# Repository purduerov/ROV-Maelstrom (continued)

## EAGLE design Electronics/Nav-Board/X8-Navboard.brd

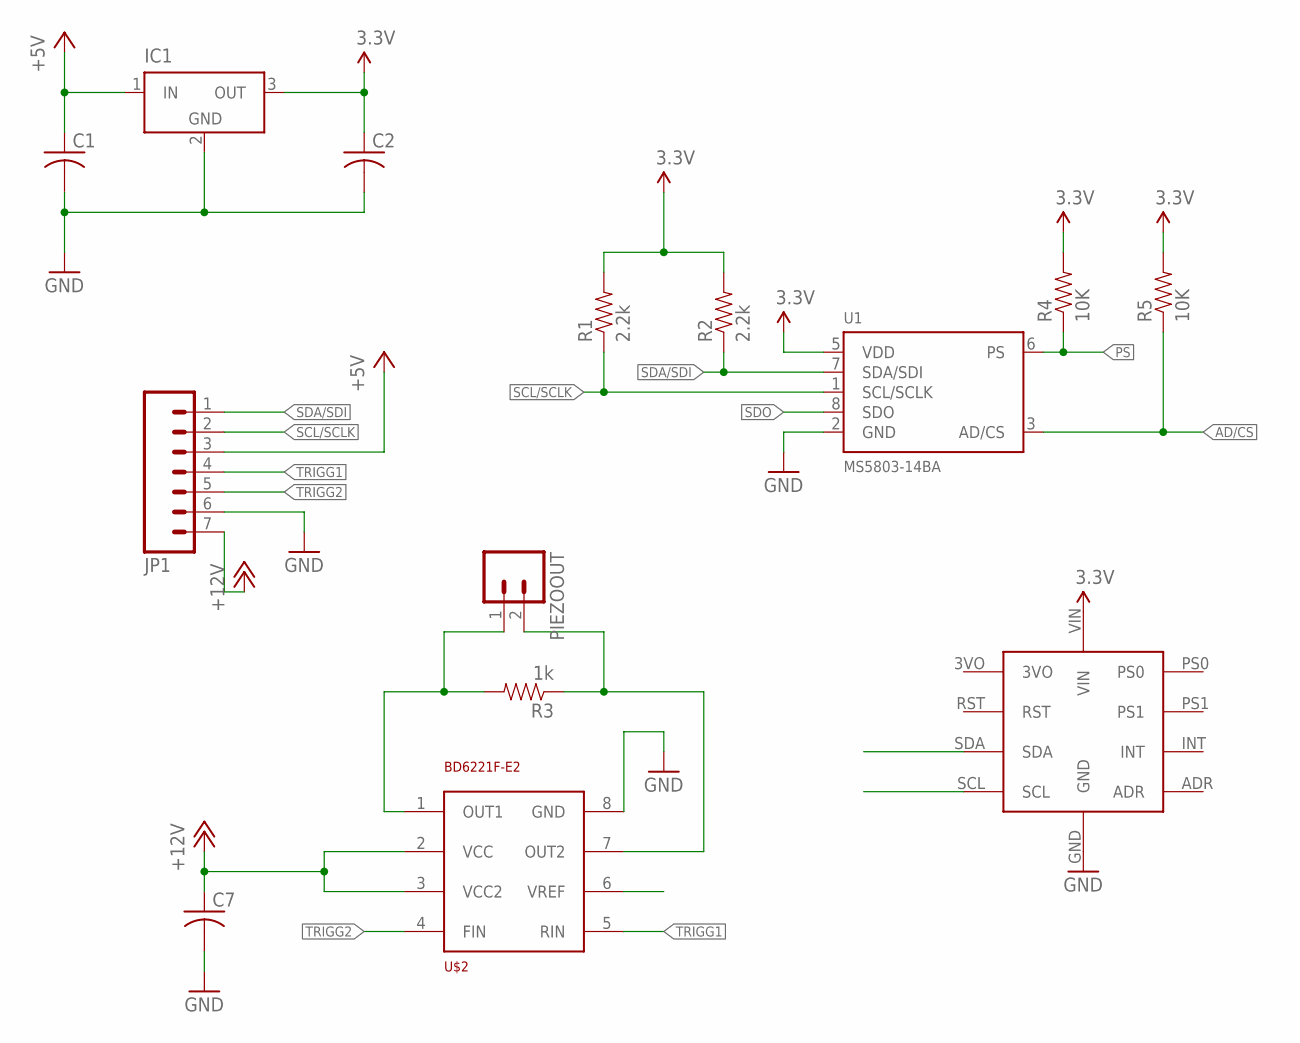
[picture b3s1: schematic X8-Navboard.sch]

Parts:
C1, C2, C7: C-USC0603; C0603
IC1: LT1129CST5; SOT223
JP1: M07; 1X07
PIEZOOUT: M02LOCK_LONGPADS; 1X02_LOCK_LONGPADS
R1, R2: 2.2k; 0603-RES
R3: 1k; 0603-RES
R4, R5: 10K; 0603-RES
U1: MS5803-14BA; MS5803
U$1: BNO055_9DOF_BREAKOUT; BNO055
U$2: BD6221F-E2; SOIC8

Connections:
3.3V: C2.1, IC1.3 (OUT), R1.2, R2.2, R4.2, R5.2, U1.5 (VDD), U$1.VIN
+5V: C1.1, IC1.1 (IN), JP1.3
+12V: C7.1, JP1.7, U$2.2 (VCC), U$2.3 (VCC2)
AD/CS: R5.1, U1.3 (AD/CS)
GND: C1.2, C2.2, C7.2, IC1.2 (GND), IC1.4 (GND), JP1.6, U1.2 (GND), U$1.GND, U$2.8 (GND)
unnamed: PIEZOOUT.1, R3.2, U$2.1 (OUT1)
unnamed: PIEZOOUT.2, R3.1, U$2.7 (OUT2)
PS: R4.1, U1.6 (PS)
SCL/SCLK: JP1.2, R1.1, U1.1 (SCL/SCLK), U$1.SCL
SDA/SDI: JP1.1, R2.1, U1.7 (SDA/SDI), U$1.SDA
SDO: U1.8 (SDO)
TRIGG1: JP1.4, U$2.5 (RIN)
TRIGG2: JP1.5, U$2.4 (FIN)

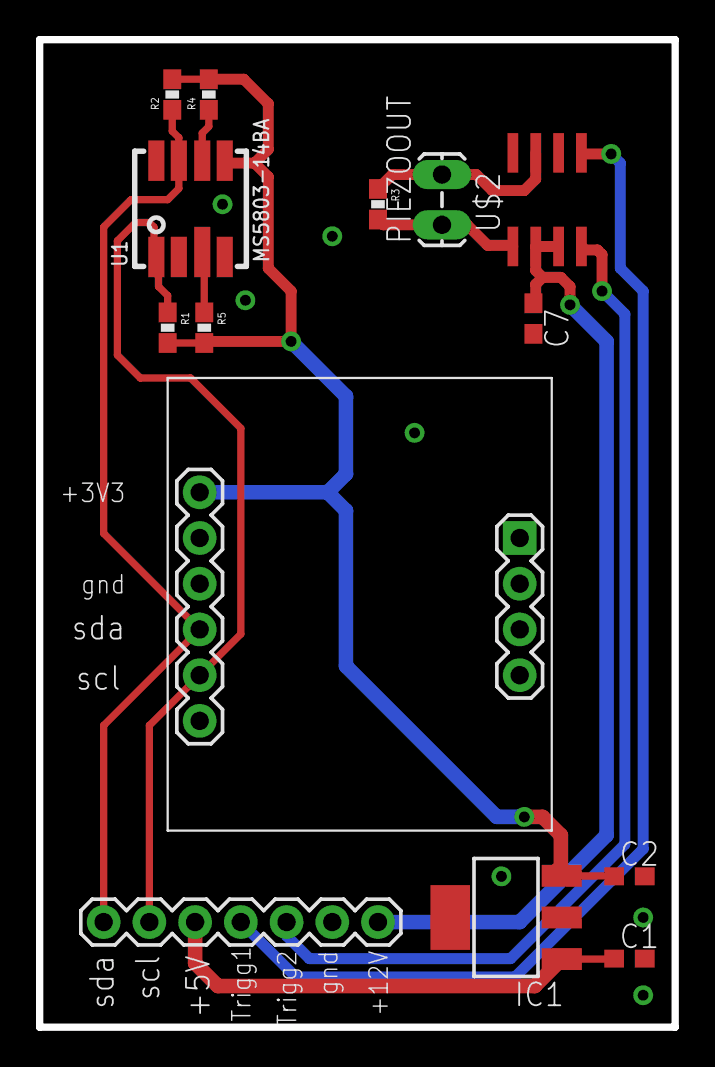
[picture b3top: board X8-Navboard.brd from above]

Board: 2 copper layers, 35.3 x 54.9 mm, 14 parts (0 on the bottom side), 12 nets.

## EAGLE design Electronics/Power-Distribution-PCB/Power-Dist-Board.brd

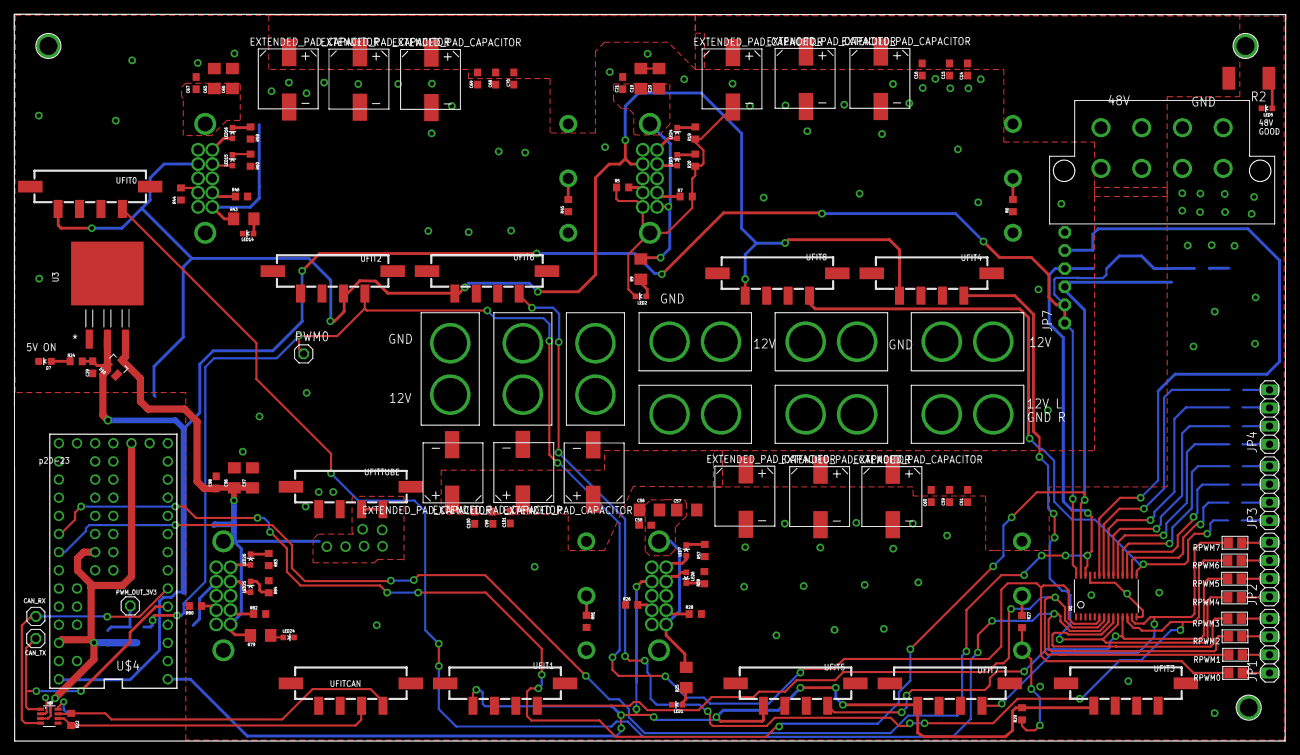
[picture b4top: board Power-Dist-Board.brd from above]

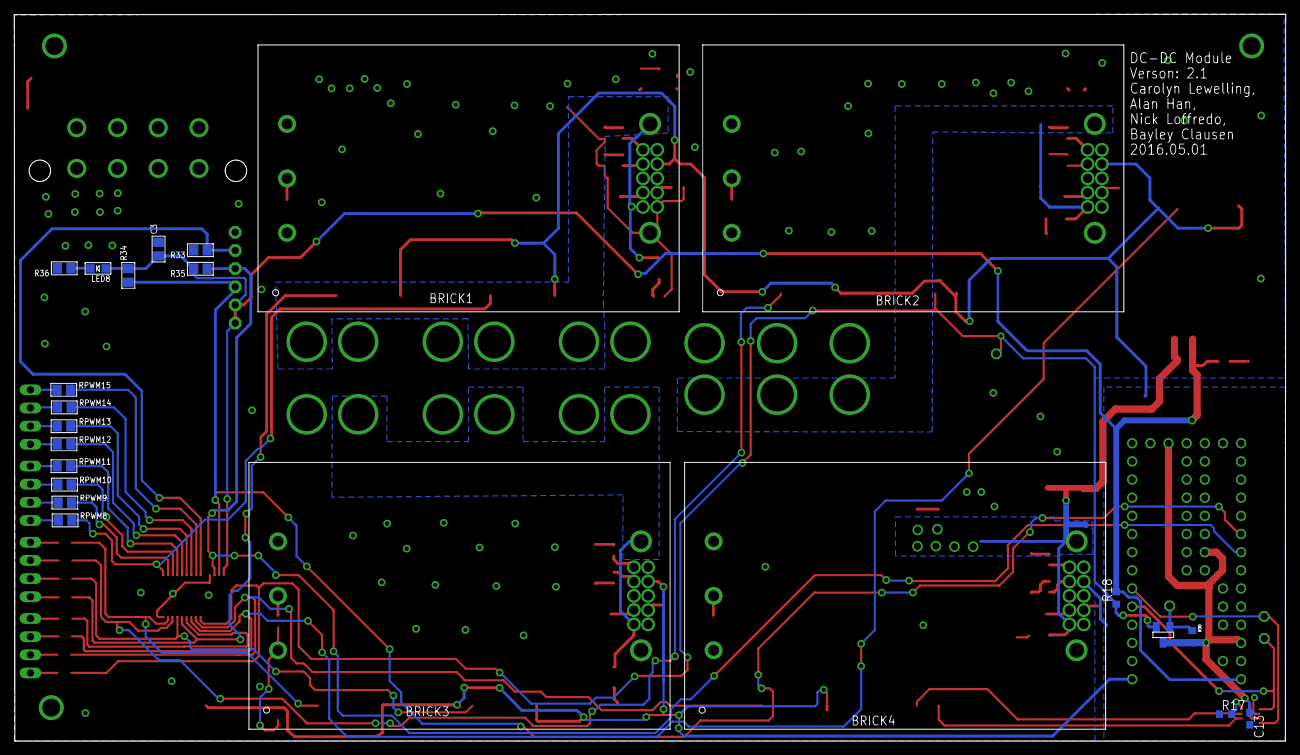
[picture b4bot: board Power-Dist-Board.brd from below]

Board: 2 copper layers, 177.9 x 101.7 mm, 148 parts (23 on the bottom side), 85 nets.

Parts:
BRICK1, BRICK2, BRICK3, BRICK4: BRICK_DC-DC_CONVERTER
C3: 10uF; 0805
C13: 0.1uF; C0603
C14, C15, C16: .1uF; C0603
C19, C20: 15uF; C3216
C21: 10uF; C0603
C22V1, C22V2, C22V3, C22V4, C22V5, C22V6, C22V7, C22V8, C22V9, C22V10, C22V11, C22V12: EXTENDED_PAD_CAPACITOR; MODIFIED-NICHICON-UX-8X10
C29: 0.1u; C0603
C56, C57, C65, C66, C96, C97: 15u; C3216
C58, C67, C98: 10u; C0603
C59, C60, C61, C68, C69, C70, C99, C100, C101: .1u; C0603
CAN_RX: 1X01
CAN_TX: 1X01
D7: RED; LED-0603
D10: BAS40; SOT23
JP1, JP2, JP3, JP4: 1X04
JP7: 1X06-CLEANBIG
LED1, LED2, LED3, LED5, LED6, LED14, LED15, LED24, LED25: GREEN; LED-0603
LED4, LED7, LED16, LED26: RED; LED-0603
LED8: VCC; CHIPLED_0805
PWM0: 1X01
PWM_OUT_3V3: 1X01
R2: 2700; R2512
R5, R7, R28, R46, R82: 10k; R0603
R6, R27, R29, R45, R81: 0; R0603
R9, R25, R43, R79: 1.1k; R1206
R17, R22: 120; R0603
R18, R30: 10K; R0603
R19, R20, R57, R58, R59, R60, R83, R84: 1k; R0603
R24: 330; R0603
R26: 33k; R0603
R33, R34, R35: 10K; 0805
R36: 220; 0805
R44: 22k; R0603
R80: 47k; R0603
RPWM0, RPWM1, RPWM2, RPWM3, RPWM4, RPWM5, RPWM6, RPWM7, RPWM8, RPWM9, RPWM10, RPWM11, RPWM12, RPWM13, RPWM14, RPWM15: 220; 0805
U1: PCA9685; TSSOP28
U3: LM1085IS-5.0; TO254P1435X457-3N
U$2, U$3, U$10, U$11, U$16, U$17, U$18, U$19, U$21: XT60
U$4: TEENSY_3.1_ALL_PINS_AND_PADS; TEENSY3_ALL_PINS_&_PADS
U$8: MAX3051MAX3051; SOT23-8L
U$12: BSS138; SOT-23-BSS138
U$13: MEGA-FIT-8
U$100, U$101, U$102: MOUNTINGHOLE2.5; MOUNTINGHOLE_2.5_PLATED
UFIT0, UFIT1, UFIT2, UFIT3, UFIT4, UFIT5, UFIT6, UFIT7, UFIT8: MICRO-FIT-4-SMD-HZVT; MICRO-FIT-4-SMD(CORRECTED)
UFITCAN: MICRO-FIT-4-SMD-HZVT; MICRO-FIT-4-SMD(CORRECTED)
UFITTUBE: MICRO-FIT-4-SMD-HZVT; MICRO-FIT-4-SMD(CORRECTED)

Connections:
+3V3: C13.1, R30.2, U$4.3.3V, U$4.3.3V1, U$4.3.3V2, U$8.3, U$12.1
+5V: C3.1, C29.2, D10.1, JP7.1, JP7.2, LED8.A, R18.2, R24.2, R34.2, R35.2, U1.28, U3.2, U$4.VIN
+12V1: BRICK1.6, BRICK1.16, C19.1, C20.1, C21.1, R9.2, U$2.P$2, U$3.P$2, U$10.P$2
+12V2: BRICK2.6, BRICK2.16, C65.1, C66.1, C67.1, R43.2, U$11.P$2, U$16.P$2, U$17.P$2
+12V3: BRICK3.6, BRICK3.16, C56.1, C57.1, C58.1, R25.2, U$18.P$2, U$19.P$2, U$21.P$2
+12V4: BRICK4.6, BRICK4.16, C96.1, C97.1, C98.1, D10.3, R79.2, U3.3, UFITTUBE.C3, UFITTUBE.C4
+48V: BRICK1.1, BRICK2.1, BRICK3.1, BRICK4.1, C14.1, C15.1, C16.1, C22V1.P$3, C22V2.P$3, C22V3.P$3, C22V4.P$3, C22V5.P$3, C22V6.P$3, C22V7.P$3, C22V8.P$3, C22V9.P$3, C22V10.P$3, C22V11.P$3, C22V12.P$3, C59.1, C60.1, C61.1, C68.1, C69.1, C70.1, C99.1, C100.1, C101.1, R2.2, U$13.P1, U$13.P2, U$13.P5, U$13.P6
ADRS00A: BRICK1.8, R7.2
ADRS00A1: BRICK3.8, R28.2
ADRS00A4: BRICK2.8, R46.2
ADRS00A5: BRICK4.8, R82.2
ADRS00B: BRICK1.9, R5.2
ADRS00B1: BRICK3.9, R26.2
ADRS00B4: BRICK2.9, R44.2
ADRS00B5: BRICK4.9, R80.2
ALERT: BRICK1.14, LED4.A
ALERT2: BRICK2.14, LED16.A
ALERT3: BRICK3.14, LED7.A
ALERT4: BRICK4.14, LED26.A
CANH: R22.2, U$8.7, UFITCAN.C4
CANL: R22.1, U$8.6, UFITCAN.C3
DGND: BRICK1.13, BRICK2.13, BRICK3.13, BRICK4.13, C13.2, R17.1, R29.2, U$4.GND, U$4.GND1, U$4.GND2, U$8.2, UFIT0.C1, UFIT1.C1, UFIT2.C3, UFIT3.C1, UFIT4.C1, UFIT5.C1, UFIT6.C1, UFIT7.C1, UFIT8.C1
GND: BRICK1.4, BRICK1.5, BRICK1.7, BRICK2.4, BRICK2.5, BRICK2.7, BRICK3.4, BRICK3.5, BRICK3.7, BRICK4.4, BRICK4.5, BRICK4.7, C3.2, C14.2, C15.2, C16.2, C19.2, C20.2, C21.2, C22V1.P$1, C22V2.P$1, C22V3.P$1, C22V4.P$1, C22V5.P$1, C22V6.P$1, C22V7.P$1, C22V8.P$1, C22V9.P$1, C22V10.P$1, C22V11.P$1, C22V12.P$1, C29.1, C56.2, C57.2, C58.2, C59.2, C60.2, C61.2, C65.2, C66.2, C67.2, C68.2, C69.2, C70.2, C96.2, C97.2, C98.2, C99.2, C100.2, C101.2, D7.C, JP7.6, LED1.C, LED2.C, LED5.C, LED14.C, LED24.C, R5.1, R6.1, R7.1, R19.1, R20.1, R26.1, R27.1, R28.1, R29.1, R33.2, R36.2, R44.1, R45.1, R46.1, R57.1, R58.1, R59.1, R60.1, R80.1, R81.1, R82.1, R83.1, R84.1, U1.1, U1.2, U1.3, U1.4, U1.5, U1.14, U1.24, U1.25, U3.1, U$2.P$1, U$3.P$1, U$10.P$1, U$11.P$1, U$13.P3, U$13.P4, U$13.P7, U$13.P8, U$16.P$1, U$17.P$1, U$18.P$1, U$19.P$1, U$21.P$1, UFITTUBE.C1, UFITTUBE.C2
unnamed: BRICK1.2, R6.2
unnamed: LED5.A, R2.1
unnamed: LED4.C, R19.2
unnamed: LED3.C, R20.2
unnamed: LED1.A, R25.1
unnamed: LED2.A, R9.1
unnamed: BRICK3.2, R27.2
unnamed: LED8.C, R36.1
unnamed: JP2.3, RPWM6.1
unnamed: JP2.4, RPWM7.1
unnamed: JP2.2, RPWM5.1
unnamed: D7.A, R24.1
unnamed: LED14.A, R43.1
unnamed: JP2.1, RPWM4.1
unnamed: BRICK2.2, R45.2
unnamed: JP1.4, RPWM3.1
unnamed: JP1.3, RPWM2.1
unnamed: JP1.2, RPWM1.1
unnamed: JP1.1, RPWM0.1
unnamed: JP3.1, RPWM8.1
unnamed: JP3.2, RPWM9.1
unnamed: JP3.3, RPWM10.1
unnamed: LED7.C, R57.2
unnamed: LED6.C, R58.2
unnamed: LED16.C, R59.2
unnamed: LED15.C, R60.2
unnamed: JP3.4, RPWM11.1
unnamed: JP4.1, RPWM12.1
unnamed: JP4.2, RPWM13.1
unnamed: JP4.3, RPWM14.1
unnamed: JP4.4, RPWM15.1
unnamed: LED24.A, R79.1
unnamed: BRICK4.2, R81.2
unnamed: LED26.C, R83.2
unnamed: LED25.C, R84.2
unnamed: R17.2, U$8.8
OE: JP7.5, R33.1, U1.23
PG: BRICK1.12, LED3.A
PG2: BRICK2.12, LED15.A
PG3: BRICK3.12, LED6.A
PG4: BRICK4.12, LED25.A
PWM0: PWM0.1, R18.1, RPWM0.2, U1.6, U$12.2, UFIT2.C4
PWM1: RPWM1.2, U1.7, UFIT1.C4
PWM2: RPWM2.2, U1.8, UFIT0.C4
PWM3: RPWM3.2, U1.9
PWM4: RPWM4.2, U1.10, UFIT4.C4
PWM5: RPWM5.2, U1.11, UFIT5.C4
PWM6: RPWM6.2, U1.12, UFIT6.C4
PWM7: RPWM7.2, U1.13, UFIT7.C4
PWM8: RPWM8.2, U1.15, UFIT8.C4
PWM9: RPWM9.2, U1.16
PWM10: RPWM10.2, U1.17
PWM11: RPWM11.2, U1.18
PWM12: RPWM12.2, U1.19
PWM13: RPWM13.2, U1.20
PWM14: RPWM14.2, U1.21
PWM15: RPWM15.2, U1.22
PWM_IN: PWM_OUT_3V3.1, R30.1, U$12.3
RXD: CAN_RX.1, U$4.4, U$8.4
SCL: JP7.4, R35.1, U1.26, U$4.19/A5
SDA: JP7.3, R34.1, U1.27, U$4.18/A4
TXD: CAN_TX.1, U$4.3, U$8.1

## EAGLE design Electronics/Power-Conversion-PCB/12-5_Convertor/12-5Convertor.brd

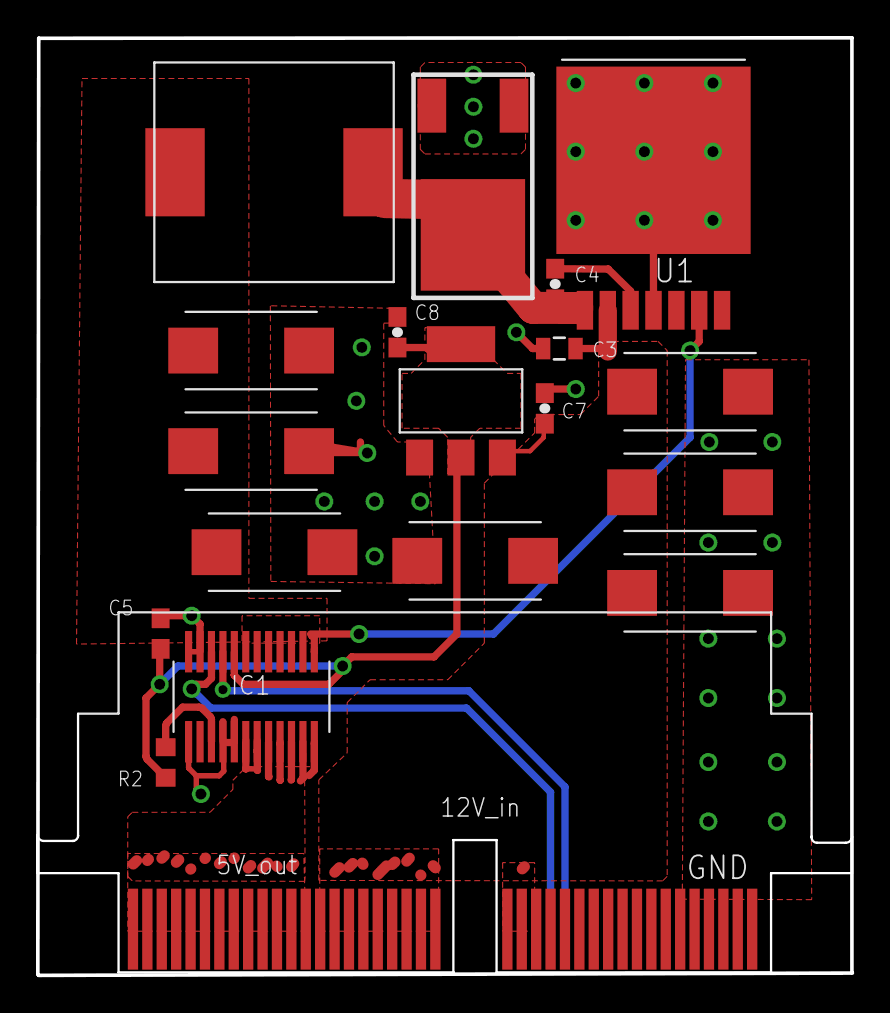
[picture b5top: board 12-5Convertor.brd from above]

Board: 2 copper layers, 45.3 x 52.1 mm, 19 parts (0 on the bottom side), 10 nets.

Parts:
C2, C11, C12, C13: 10uF; CTAN(7.30_4.30MM)
C3: 0.47uF; 0805
C4: 0.01uF; 0603-CAP
C5: 0.1uF; C0603
C6, C9, C10: 150uF; CTAN(7.30_4.30MM)
C7, C8: 1uF; 0603-CAP
IC1: ACS764; SSOP24
R2: 10kOhm; R0603
U1: LM2678
U$1: SWITCHMODE_SCHOTTKY; DPAK-3
U$2: 15uH; HCMA1305
U$3: NCP1117
U$4: HSCPART; HSC8-40PINOUUT

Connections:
+3V3: C5.1, C8.1, IC1.8, R2.2, U$3.OUT, U$3.TAB
+5V: IC1.18, IC1.19, IC1.20, IC1.21, IC1.22, IC1.23, IC1.24, U$4.T1, U$4.T2, U$4.T3, U$4.T4, U$4.T5, U$4.T6, U$4.T7, U$4.T8, U$4.T9, U$4.T10, U$4.T11, U$4.T12, U$4.T13
+12V: C2.+, C3.1, C7.1, C11.+, C12.+, C13.+, U1.2, U$3.INPUT, U$4.T14, U$4.T15, U$4.T16, U$4.T17, U$4.T18, U$4.T19, U$4.T20, U$4.T21, U$4.T22, U$4.T23, U$4.T24, U$4.T25
FAULT: IC1.15, R2.1
GND: C2.-, C3.2, C5.2, C6.-, C7.2, C8.2, C9.-, C10.-, C11.-, C12.-, C13.-, IC1.11, IC1.12, IC1.13, IC1.16, IC1.17, U1.4, U1.TAB, U$1.P$1, U$1.P$3, U$3.GND, U$4.B28, U$4.B29, U$4.B30, U$4.B31, U$4.B32, U$4.B33, U$4.B34, U$4.B35, U$4.B36, U$4.B37, U$4.B38, U$4.B39, U$4.B40
unnamed: C4.1, U1.3
unnamed: C4.2, U1.1, U$1.P$4, U$2.P$1
SCL: IC1.10, U$4.B26
SDA: IC1.9, U$4.B27
VOUT: C6.+, C9.+, C10.+, IC1.1, IC1.2, IC1.3, IC1.4, IC1.5, IC1.6, IC1.7, U1.6, U$2.P$2

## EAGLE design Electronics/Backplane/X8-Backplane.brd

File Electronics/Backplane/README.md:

# PCB-X8-Backplane
The board to attach all boards. Note: May not actually be a backplane!

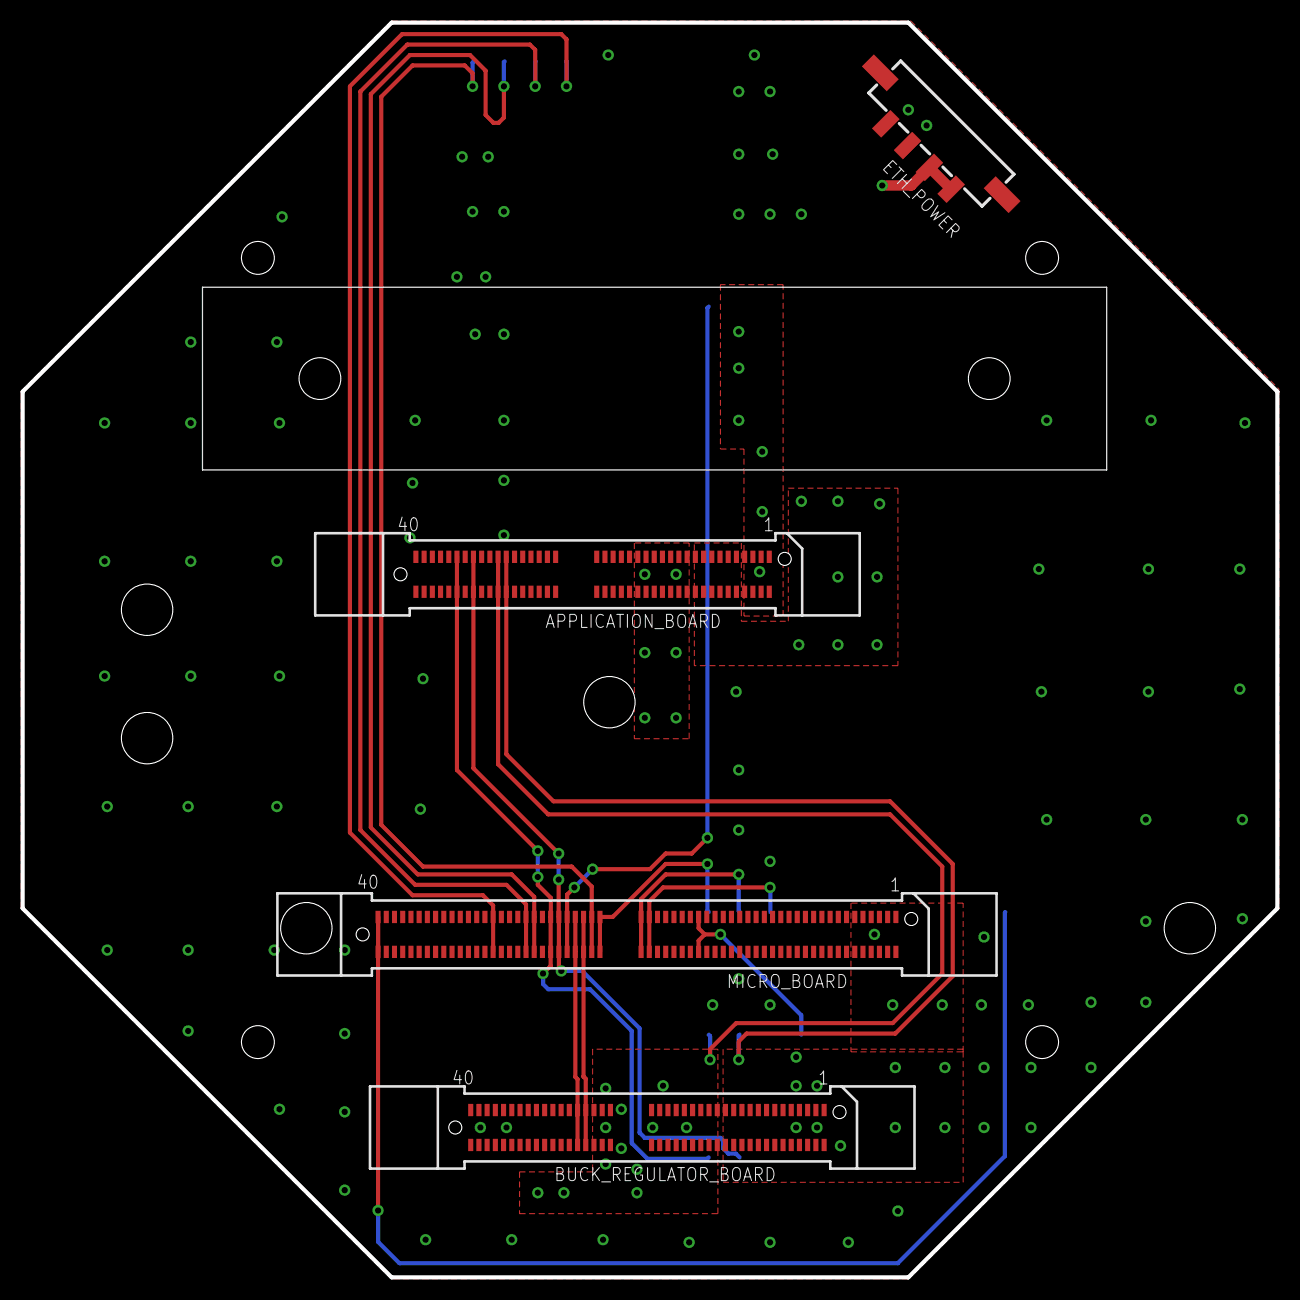
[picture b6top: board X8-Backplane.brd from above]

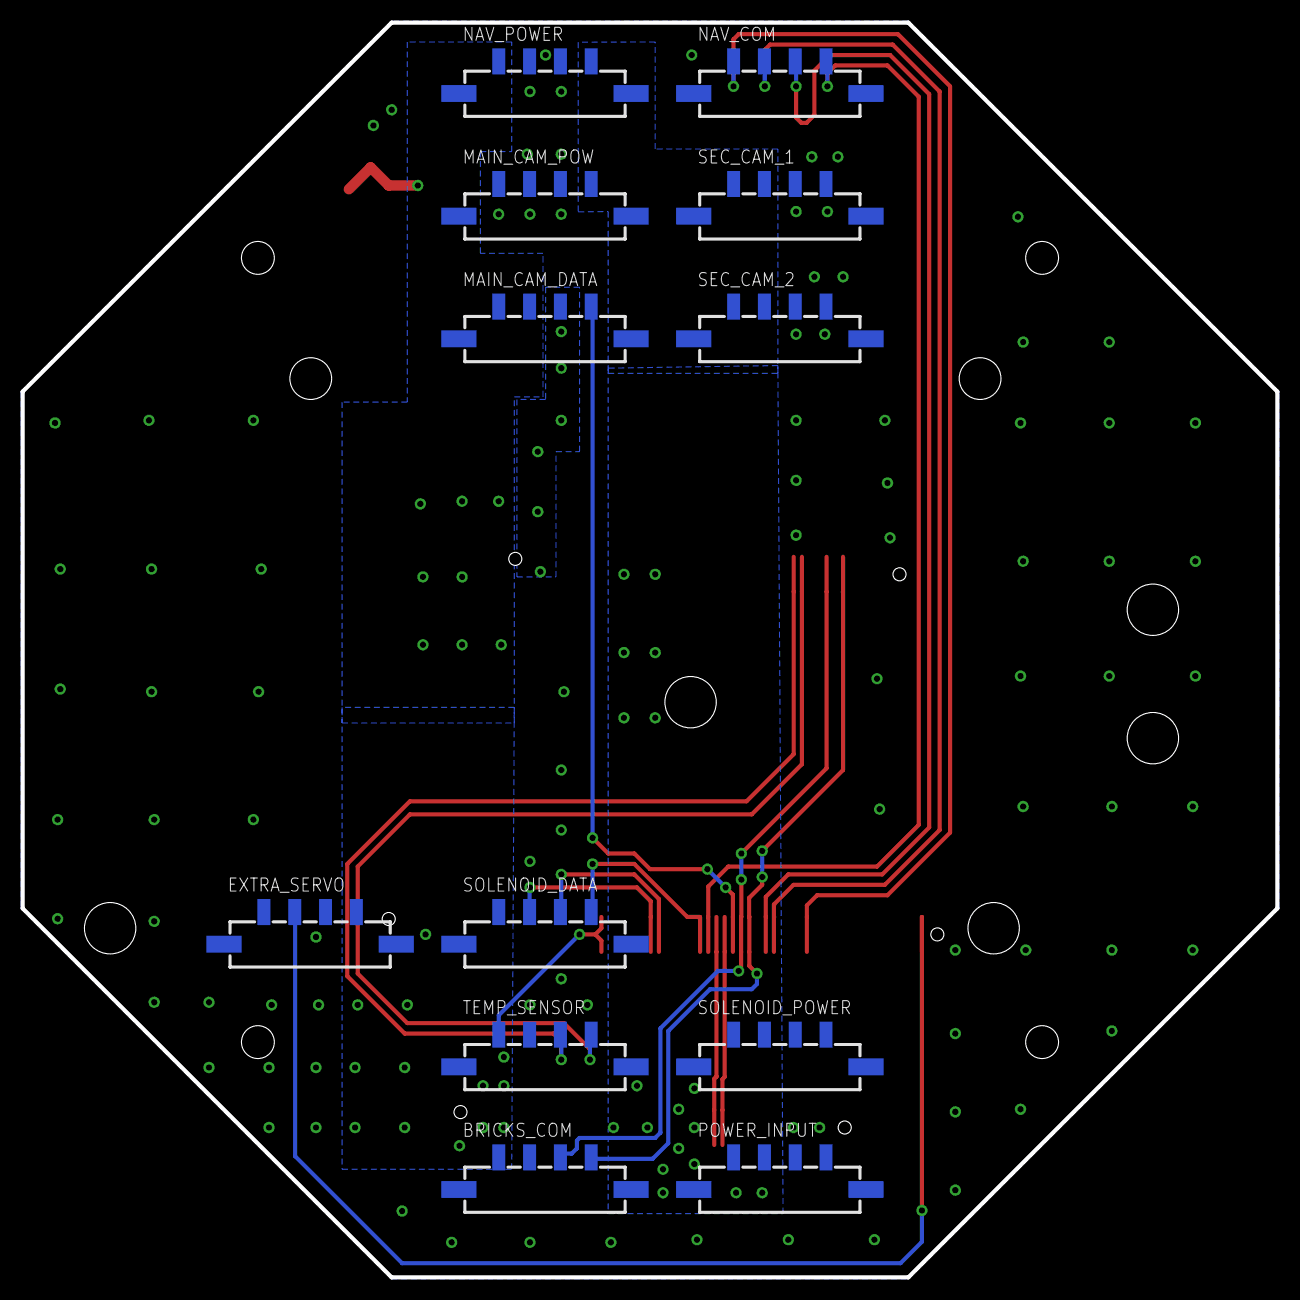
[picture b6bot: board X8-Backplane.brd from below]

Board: 2 copper layers, 122.1 x 122.1 mm, 17 parts (12 on the bottom side), 20 nets.

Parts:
APPLICATION_BOARD: HSEC8-140-01-XX-DV-A
BRICKS_COM: MICRO-FIT-4-SMD-PART; MICRO-FIT-4-SMD
BUCK_REGULATOR_BOARD: HSEC8-140-01-XX-DV-A
ETH_POWER: MICRO-FIT-4-SMD-PART; MICRO-FIT-4-SMD
EXTRA_SERVO: MICRO-FIT-4-SMD-PART; MICRO-FIT-4-SMD
MAIN_CAM_DATA: MICRO-FIT-4-SMD-PART; MICRO-FIT-4-SMD
MAIN_CAM_POW: MICRO-FIT-4-SMD-PART; MICRO-FIT-4-SMD
MICRO_BOARD: HSEC8-160-01-XX-DV-A
NAV_COM: MICRO-FIT-4-SMD-PART; MICRO-FIT-4-SMD
NAV_POWER: MICRO-FIT-4-SMD-PART; MICRO-FIT-4-SMD
POWER_INPUT: MICRO-FIT-4-SMD-PART; MICRO-FIT-4-SMD
SEC_CAM_1, SEC_CAM_2: MICRO-FIT-4-SMD-PART; MICRO-FIT-4-SMD
SOLENOID_DATA: MICRO-FIT-4-SMD-PART; MICRO-FIT-4-SMD
SOLENOID_POWER: MICRO-FIT-4-SMD-PART; MICRO-FIT-4-SMD
TEMP_SENSOR: MICRO-FIT-4-SMD-PART; MICRO-FIT-4-SMD
U$18: ETH_SWITCH

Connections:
+3V3: APPLICATION_BOARD.57, APPLICATION_BOARD.58, TEMP_SENSOR.C3
+5V: APPLICATION_BOARD.9, APPLICATION_BOARD.10, APPLICATION_BOARD.11, APPLICATION_BOARD.12, APPLICATION_BOARD.13, APPLICATION_BOARD.14, APPLICATION_BOARD.15, APPLICATION_BOARD.16, APPLICATION_BOARD.17, APPLICATION_BOARD.18, APPLICATION_BOARD.19, APPLICATION_BOARD.20, BUCK_REGULATOR_BOARD.1, BUCK_REGULATOR_BOARD.2, BUCK_REGULATOR_BOARD.3, BUCK_REGULATOR_BOARD.4, BUCK_REGULATOR_BOARD.5, BUCK_REGULATOR_BOARD.6, BUCK_REGULATOR_BOARD.7, BUCK_REGULATOR_BOARD.8, BUCK_REGULATOR_BOARD.9, BUCK_REGULATOR_BOARD.10, BUCK_REGULATOR_BOARD.11, BUCK_REGULATOR_BOARD.12, BUCK_REGULATOR_BOARD.13, BUCK_REGULATOR_BOARD.14, BUCK_REGULATOR_BOARD.15, BUCK_REGULATOR_BOARD.16, BUCK_REGULATOR_BOARD.17, BUCK_REGULATOR_BOARD.18, BUCK_REGULATOR_BOARD.19, BUCK_REGULATOR_BOARD.20, BUCK_REGULATOR_BOARD.21, BUCK_REGULATOR_BOARD.22, BUCK_REGULATOR_BOARD.23, BUCK_REGULATOR_BOARD.24, BUCK_REGULATOR_BOARD.25, BUCK_REGULATOR_BOARD.26, ETH_POWER.C1, ETH_POWER.C2, EXTRA_SERVO.C4, MAIN_CAM_DATA.C1, MAIN_CAM_DATA.C2, MICRO_BOARD.1, MICRO_BOARD.2, MICRO_BOARD.3, MICRO_BOARD.4, MICRO_BOARD.5, MICRO_BOARD.6, MICRO_BOARD.7, MICRO_BOARD.8, MICRO_BOARD.9, MICRO_BOARD.10, MICRO_BOARD.11, MICRO_BOARD.12, NAV_POWER.C1, SOLENOID_DATA.C1
+12V: APPLICATION_BOARD.21, APPLICATION_BOARD.22, APPLICATION_BOARD.23, APPLICATION_BOARD.24, APPLICATION_BOARD.25, APPLICATION_BOARD.26, APPLICATION_BOARD.27, APPLICATION_BOARD.28, APPLICATION_BOARD.29, APPLICATION_BOARD.30, APPLICATION_BOARD.31, APPLICATION_BOARD.32, APPLICATION_BOARD.33, APPLICATION_BOARD.34, BUCK_REGULATOR_BOARD.27, BUCK_REGULATOR_BOARD.28, BUCK_REGULATOR_BOARD.29, BUCK_REGULATOR_BOARD.30, BUCK_REGULATOR_BOARD.31, BUCK_REGULATOR_BOARD.32, BUCK_REGULATOR_BOARD.33, BUCK_REGULATOR_BOARD.34, BUCK_REGULATOR_BOARD.35, BUCK_REGULATOR_BOARD.36, BUCK_REGULATOR_BOARD.37, BUCK_REGULATOR_BOARD.38, BUCK_REGULATOR_BOARD.39, BUCK_REGULATOR_BOARD.40, BUCK_REGULATOR_BOARD.41, BUCK_REGULATOR_BOARD.42, BUCK_REGULATOR_BOARD.43, BUCK_REGULATOR_BOARD.44, BUCK_REGULATOR_BOARD.45, BUCK_REGULATOR_BOARD.46, BUCK_REGULATOR_BOARD.47, BUCK_REGULATOR_BOARD.48, BUCK_REGULATOR_BOARD.49, BUCK_REGULATOR_BOARD.50, MAIN_CAM_POW.C4, NAV_POWER.C4, POWER_INPUT.C1, POWER_INPUT.C2, SEC_CAM_1.C1, SEC_CAM_1.C2, SEC_CAM_2.C1, SEC_CAM_2.C2, SOLENOID_POWER.C1, SOLENOID_POWER.C2
BACK_UP_TEMP_DATA: MICRO_BOARD.49, MICRO_BOARD.50, TEMP_SENSOR.C1
BUCK_SCL: BUCK_REGULATOR_BOARD.53, BUCK_REGULATOR_BOARD.54, MICRO_BOARD.71, MICRO_BOARD.72
BUCK_SDA: BUCK_REGULATOR_BOARD.51, BUCK_REGULATOR_BOARD.52, MICRO_BOARD.69, MICRO_BOARD.70
CANH: APPLICATION_BOARD.69, APPLICATION_BOARD.70, BRICKS_COM.C4, MICRO_BOARD.77, MICRO_BOARD.78
CANL: APPLICATION_BOARD.65, APPLICATION_BOARD.66, BRICKS_COM.C3, MICRO_BOARD.75, MICRO_BOARD.76
CLK: MICRO_BOARD.63, MICRO_BOARD.64, SOLENOID_DATA.C3
DATA: MICRO_BOARD.65, MICRO_BOARD.66, SOLENOID_DATA.C4
ENABLE: MICRO_BOARD.61, MICRO_BOARD.62, SOLENOID_DATA.C2
GND: APPLICATION_BOARD.37, APPLICATION_BOARD.38, APPLICATION_BOARD.39, APPLICATION_BOARD.40, APPLICATION_BOARD.41, APPLICATION_BOARD.42, APPLICATION_BOARD.43, APPLICATION_BOARD.44, APPLICATION_BOARD.45, APPLICATION_BOARD.46, APPLICATION_BOARD.47, APPLICATION_BOARD.48, APPLICATION_BOARD.49, APPLICATION_BOARD.50, APPLICATION_BOARD.51, APPLICATION_BOARD.52, BUCK_REGULATOR_BOARD.55, BUCK_REGULATOR_BOARD.56, BUCK_REGULATOR_BOARD.57, BUCK_REGULATOR_BOARD.58, BUCK_REGULATOR_BOARD.59, BUCK_REGULATOR_BOARD.60, BUCK_REGULATOR_BOARD.61, BUCK_REGULATOR_BOARD.62, BUCK_REGULATOR_BOARD.63, BUCK_REGULATOR_BOARD.64, BUCK_REGULATOR_BOARD.65, BUCK_REGULATOR_BOARD.66, BUCK_REGULATOR_BOARD.67, BUCK_REGULATOR_BOARD.68, BUCK_REGULATOR_BOARD.69, BUCK_REGULATOR_BOARD.70, BUCK_REGULATOR_BOARD.71, BUCK_REGULATOR_BOARD.72, BUCK_REGULATOR_BOARD.73, BUCK_REGULATOR_BOARD.74, BUCK_REGULATOR_BOARD.75, BUCK_REGULATOR_BOARD.76, BUCK_REGULATOR_BOARD.77, BUCK_REGULATOR_BOARD.78, BUCK_REGULATOR_BOARD.79, BUCK_REGULATOR_BOARD.80, ETH_POWER.C3, ETH_POWER.C4, EXTRA_SERVO.C3, MAIN_CAM_POW.C1, MAIN_CAM_POW.C2, MAIN_CAM_POW.C3, MICRO_BOARD.21, MICRO_BOARD.22, MICRO_BOARD.23, MICRO_BOARD.24, MICRO_BOARD.25, MICRO_BOARD.26, MICRO_BOARD.27, MICRO_BOARD.28, MICRO_BOARD.29, MICRO_BOARD.30, MICRO_BOARD.31, MICRO_BOARD.32, MICRO_BOARD.33, MICRO_BOARD.34, MICRO_BOARD.35, MICRO_BOARD.36, NAV_POWER.C2, NAV_POWER.C3, POWER_INPUT.C3, POWER_INPUT.C4, SEC_CAM_1.C3, SEC_CAM_1.C4, SEC_CAM_2.C3, SEC_CAM_2.C4, SOLENOID_POWER.C3, SOLENOID_POWER.C4, TEMP_SENSOR.C2
LED_PWM: APPLICATION_BOARD.1, APPLICATION_BOARD.2, APPLICATION_BOARD.3, APPLICATION_BOARD.4, APPLICATION_BOARD.5, APPLICATION_BOARD.6, APPLICATION_BOARD.7, APPLICATION_BOARD.8, MAIN_CAM_DATA.C3
MAIN_SERVO: MAIN_CAM_DATA.C4, MICRO_BOARD.73, MICRO_BOARD.74
NAV_SCL: MICRO_BOARD.83, MICRO_BOARD.84, NAV_COM.C2
NAV_SDA: MICRO_BOARD.81, MICRO_BOARD.82, NAV_COM.C3
SECOND_SERVO: EXTRA_SERVO.C2, MICRO_BOARD.119, MICRO_BOARD.120
SONAR_DAC: MICRO_BOARD.91, MICRO_BOARD.92, NAV_COM.C1
SONAR_PWM: MICRO_BOARD.67, MICRO_BOARD.68, NAV_COM.C4
TEMP_DATA: APPLICATION_BOARD.59, APPLICATION_BOARD.60, TEMP_SENSOR.C4

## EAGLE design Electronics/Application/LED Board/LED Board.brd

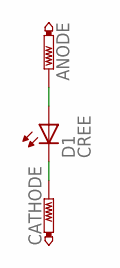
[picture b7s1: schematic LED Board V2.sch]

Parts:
ANODE: PTR1PAD1-20; P1-20
CATHODE: PTR1PAD1-20; P1-20
D1: CREE; CREE-XLAMP-XM-L

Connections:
CAM_LEDV: ANODE.TP, D1.A, D1.A@1 (A)
GND: CATHODE.TP, D1.C, D1.C1 (C), D1.C@1 (C)

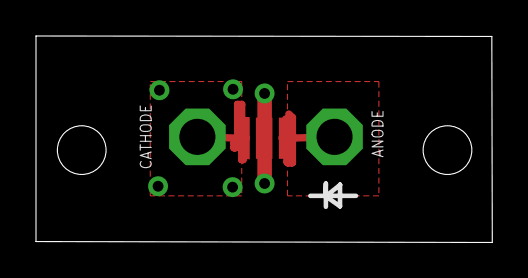
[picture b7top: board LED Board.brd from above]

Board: 2 copper layers, 25.3 x 11.5 mm, 3 parts (0 on the bottom side), 2 nets.

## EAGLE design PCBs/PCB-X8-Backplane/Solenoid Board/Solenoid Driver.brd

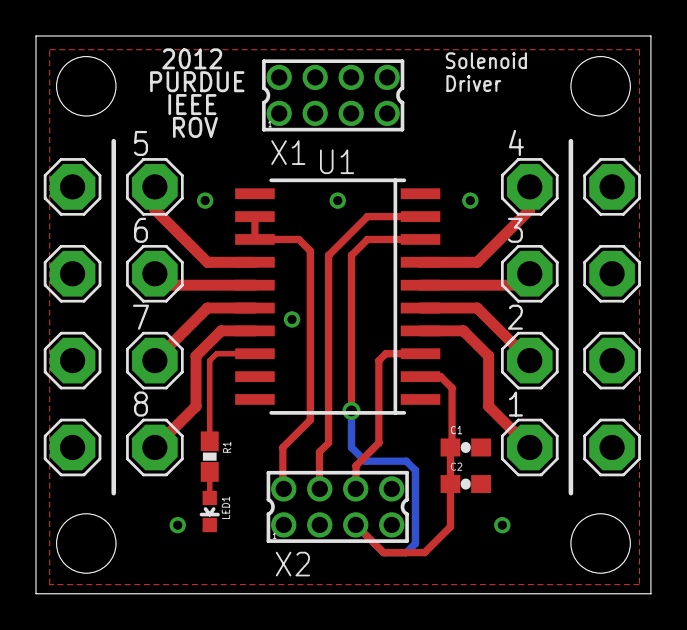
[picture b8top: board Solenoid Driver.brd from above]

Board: 2 copper layers, 34.2 x 31.0 mm, 27 parts (0 on the bottom side), 16 nets.

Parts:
1, 2, 3, 4, 5, 6, 7, 8, 9, 10, 11, 12, 13, 14, 15, 16: SE14
C1: 0.1uF; 0603-CAP
C2: 10uF; 0603-CAP
JP1, JP2, JP3, JP4: STAND-OFF
LED1: Orange; LED-0603
R1: 330; 0603-RES
U1: TPIC6A596; SOIC20-W
X1, X2: 87758-0816

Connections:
5V: C1.1, C2.1, U1.2, U1.8, X2.5
CLOCK: U1.12, U1.13, X2.2
ENABLE: U1.9, X2.4
GND: C1.2, C2.2, LED1.C, U1.10, U1.11, U1.19, X1.5, X1.6, X1.7, X1.8, X2.1, X2.3
unnamed: LED1.A, R1.2
SER-IN: U1.3, X2.6
SER-OUT: R1.1, U1.18
SOL-1A: 1.MP, U1.4
SOL-1B: 2.MP, U1.5
SOL-2A: 3.MP, U1.6
SOL-2B: 4.MP, U1.7
SOL-3A: 5.MP, U1.14
SOL-3B: 6.MP, U1.15
SOL-4A: 7.MP, U1.16
SOL-4B: 8.MP, U1.17
VCC: 9.MP, 10.MP, 11.MP, 12.MP, 13.MP, 14.MP, 15.MP, 16.MP, X1.1, X1.2, X1.3, X1.4

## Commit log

2016-09-17 Add all the things
2016-09-17 Changed names
2016-09-17 Updated battlestation documentation
2016-09-17 changed to maelstrom
2016-09-27 Updated Application board
2016-09-27 updated power conversion and main micro
2016-09-27 Got rid of a bunch of things that never should have been in Github
2016-09-27 adjusted naming conventions to technical report
2016-09-27 Added key documentation
2016-09-30 Removed lots of extra stuff and trim down the size
2016-10-04 added initial mechanical stuff
2016-10-04 added parts library
2016-10-04 link to image
2016-10-06 updated readmes
2016-10-29 Removed unneeded mechanical files
2016-10-29 added some more mechanical documentation
2016-12-10 temp probe
2016-12-10 Added readmes and removed camera boxes
2016-12-10 added readme
2016-12-10 Added readmes
2016-12-10 another readme
2016-12-10 main readme
2016-12-10 readme
2016-12-27 Added more mechanical readmes
2016-12-27 Final readmes added
